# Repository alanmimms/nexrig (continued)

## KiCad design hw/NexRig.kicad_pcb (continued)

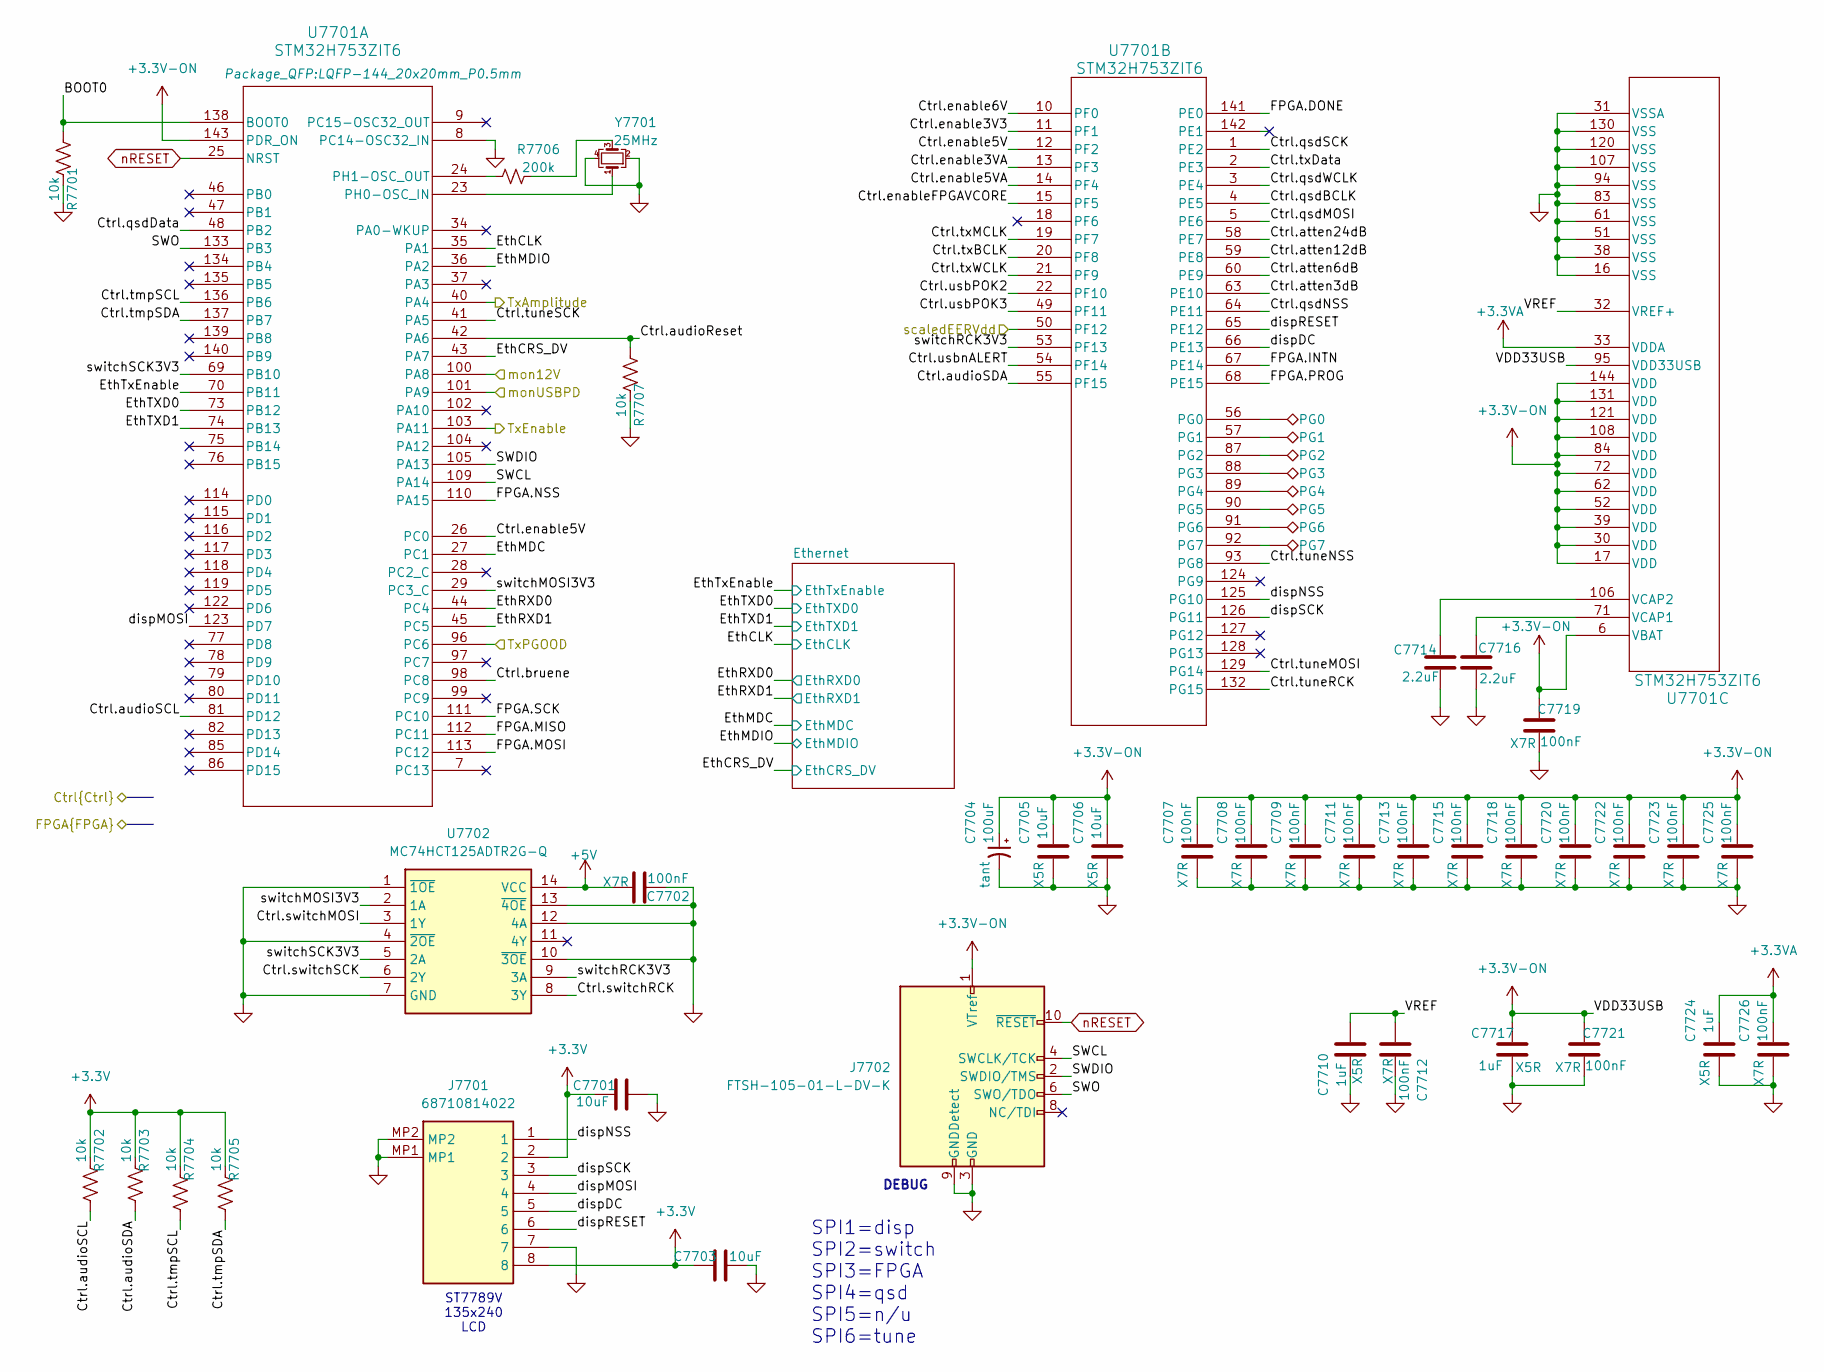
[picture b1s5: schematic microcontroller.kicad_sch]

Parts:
C7701, C7703, C7705, C7706: 10uF; C_0603_1608Metric; Manufacturer_Part_Number 81-GXT155R71E223KE1D; Mouser Part Number 963-MLAST168BB5106MT
C7702, C7707, C7708, C7709, C7711, C7712, C7713, C7715, C7718, C7719, C7720, C7721, C7722, C7723, C7725, C7726: 100nF; C_0603_1608Metric; Manufacturer_Part_Number C0805F104K1RACAUTO; Mouser Part Number 80-C0805F104K1RAUTO
C7704: 100uF; C_1206_3216Metric; Manufacturer_Part_Number TCTAL1A107M8R-V1; Mouser Part Number 755-TCTAL1A107M8R-V1
C7710, C7717, C7724: 1uF; C_0402_1005Metric; Manufacturer_Part_Number GRM155R61E105KE11D; Mouser Part Number 81-GRM155R61E105KE1D
C7714, C7716: 2.2uF; C_0805_2012Metric; Manufacturer_Part_Number TMCP1D225MTR2F; Mouser Part Number 74-TMCP1D225MTR2F
J7701: 68710814022; Mouser Part Number 710-68710814022
J7702: FTSH-105-01-L-DV-K; FTSH10501LDVK
PG7701: PG0; TestPoint_Pad_1.0x1.0mm
PG7702: PG1; TestPoint_Pad_1.0x1.0mm
PG7703: PG2; TestPoint_Pad_1.0x1.0mm
PG7704: PG3; TestPoint_Pad_1.0x1.0mm
PG7705: PG4; TestPoint_Pad_1.0x1.0mm
PG7706: PG5; TestPoint_Pad_1.0x1.0mm
PG7707: PG6; TestPoint_Pad_1.0x1.0mm
PG7708: PG7; TestPoint_Pad_1.0x1.0mm
R7701, R7702, R7703, R7704, R7705, R7707: 10k; R_0402_1005Metric
R7706: 200k; R_0603_1608Metric
U7701: STM32H753ZIT6; LQFP-144_20x20mm_P0.5mm
U7702: MC74HCT125ADTR2G-Q; SOP65P640X110-14N; Mouser Part Number 771-74HCT125PW-T
Y7701: 25MHz; Crystal_SMD_2520-4Pin_2.5x2.0mm; Manufacturer_Part_Number E2X250081G10; Mouser Part Number 504-E2X250081G10

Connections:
+3.3V: C7701.1, C7703.1, J7701.2, J7701.8, R7702.1, R7703.1, R7704.1, R7705.1; also elsewhere on the board
+3.3V-ON: C7704.1, C7705.1, C7706.1, C7707.1, C7708.1, C7709.1, C7711.1, C7713.1, C7715.1, C7717.1, C7718.1, C7719.1, C7720.1, C7721.1, C7722.1, C7723.1, C7725.1, J7702.1 (VTref), U7701.6 (VBAT), U7701.17 (VDD), U7701.30 (VDD), U7701.39 (VDD), U7701.52 (VDD), U7701.62 (VDD), U7701.72 (VDD), U7701.84 (VDD), U7701.95 (VDD33USB), U7701.108 (VDD), U7701.121 (VDD), U7701.131 (VDD), U7701.143 (PDR_ON), U7701.144 (VDD); also elsewhere on the board
+3.3VA: C7724.1, C7726.1, U7701.33 (VDDA); also elsewhere on the board
/FPGA/Ctrl.audioReset: R7707.1, U7701.42 (PA6); also elsewhere on the board
/FPGA/Ctrl.audioSCL: R7702.2, U7701.81 (PD12); also elsewhere on the board
/FPGA/Ctrl.audioSDA: R7703.2, U7701.55 (PF15); also elsewhere on the board
/FPGA/Ctrl.bruene: U7701.98 (PC8)
/FPGA/Ctrl.enable3V3: U7701.11 (PF1); also elsewhere on the board
/FPGA/Ctrl.enable3VA: U7701.13 (PF3); also elsewhere on the board
/FPGA/Ctrl.enable5V: U7701.12 (PF2), U7701.26 (PC0); also elsewhere on the board
/FPGA/Ctrl.enable5VA: U7701.14 (PF4); also elsewhere on the board
/FPGA/Ctrl.enable6V: U7701.10 (PF0); also elsewhere on the board
/FPGA/Ctrl.enableFPGAVCORE: U7701.15 (PF5)
/FPGA/Ctrl.qsdBCLK: U7701.4 (PE5); also elsewhere on the board
/FPGA/Ctrl.qsdData: U7701.48 (PB2); also elsewhere on the board
/FPGA/Ctrl.qsdMOSI: U7701.5 (PE6); also elsewhere on the board
/FPGA/Ctrl.qsdNSS: U7701.64 (PE11); also elsewhere on the board
/FPGA/Ctrl.qsdSCK: U7701.1 (PE2); also elsewhere on the board
/FPGA/Ctrl.qsdWCLK: U7701.3 (PE4); also elsewhere on the board
/FPGA/Ctrl.switchMOSI: U7702.3 (1Y); also elsewhere on the board
/FPGA/Ctrl.switchRCK: U7702.8 (3Y); also elsewhere on the board
/FPGA/Ctrl.switchSCK: U7702.6 (2Y); also elsewhere on the board
/FPGA/Ctrl.tmpSCL: R7704.2, U7701.136 (PB6); also elsewhere on the board
/FPGA/Ctrl.tmpSDA: R7705.2, U7701.137 (PB7); also elsewhere on the board
/FPGA/Ctrl.txBCLK: U7701.20 (PF8); also elsewhere on the board
/FPGA/Ctrl.txData: U7701.2 (PE3); also elsewhere on the board
/FPGA/Ctrl.txMCLK: U7701.19 (PF7); also elsewhere on the board
/FPGA/Ctrl.txWCLK: U7701.21 (PF9); also elsewhere on the board
/FPGA/Ctrl.usbPOK2: U7701.22 (PF10); also elsewhere on the board
/FPGA/Ctrl.usbPOK3: U7701.49 (PF11); also elsewhere on the board
/FPGA/Ctrl.usbnALERT: U7701.54 (PF14); also elsewhere on the board
/FPGA/FPGA.DONE: U7701.141 (PE0); also elsewhere on the board
/FPGA/FPGA.INTN: U7701.67 (PE14); also elsewhere on the board
/FPGA/FPGA.MISO: U7701.112 (PC11); also elsewhere on the board
/FPGA/FPGA.MOSI: U7701.113 (PC12); also elsewhere on the board
/FPGA/FPGA.NSS: U7701.110 (PA15); also elsewhere on the board
/FPGA/FPGA.PROG: U7701.68 (PE15); also elsewhere on the board
/FPGA/FPGA.SCK: U7701.111 (PC10); also elsewhere on the board
/Power/TxAmplitude: U7701.40 (PA4); also elsewhere on the board
/Power/TxEnable: U7701.103 (PA11); also elsewhere on the board
/Power/TxPGOOD: U7701.96 (PC6); also elsewhere on the board
/Power/mon12V: U7701.100 (PA8); also elsewhere on the board
/Power/monUSBPD: U7701.101 (PA9); also elsewhere on the board
/Power/scaledEERVdd: U7701.50 (PF12); also elsewhere on the board
/microcontroller/BOOT0: R7701.1, U7701.138 (BOOT0)
/microcontroller/Ctrl.atten3dB: U7701.63 (PE10)
/microcontroller/Ctrl.atten6dB: U7701.60 (PE9)
/microcontroller/Ctrl.atten12dB: U7701.59 (PE8)
/microcontroller/Ctrl.atten24dB: U7701.58 (PE7)
/microcontroller/Ctrl.tuneMOSI: U7701.129 (PG14)
/microcontroller/Ctrl.tuneNSS: U7701.93 (PG8)
/microcontroller/Ctrl.tuneRCK: U7701.132 (PG15)
/microcontroller/Ctrl.tuneSCK: U7701.41 (PA5)
/microcontroller/EthCLK: U7701.35 (PA1); also elsewhere on the board
/microcontroller/EthCRS_DV: U7701.43 (PA7); also elsewhere on the board
/microcontroller/EthMDC: U7701.27 (PC1); also elsewhere on the board
/microcontroller/EthMDIO: U7701.36 (PA2); also elsewhere on the board
/microcontroller/EthRXD0: U7701.44 (PC4); also elsewhere on the board
/microcontroller/EthRXD1: U7701.45 (PC5); also elsewhere on the board
/microcontroller/EthTXD0: U7701.73 (PB12); also elsewhere on the board
/microcontroller/EthTXD1: U7701.74 (PB13); also elsewhere on the board
/microcontroller/EthTxEnable: U7701.70 (PB11); also elsewhere on the board
/microcontroller/SWCL: J7702.4 (SWCLK/TCK), U7701.109 (PA14)
/microcontroller/SWDIO: J7702.2 (SWDIO/TMS), U7701.105 (PA13)
/microcontroller/SWO: J7702.6 (SWO/TDO), U7701.133 (PB3)
/microcontroller/VREF: C7710.1, C7712.1, U7701.32 (VREF+)
/microcontroller/dispDC: J7701.5, U7701.66 (PE13)
/microcontroller/dispMOSI: J7701.4, U7701.123 (PD7)
/microcontroller/dispNSS: J7701.1, U7701.125 (PG10)
/microcontroller/dispRESET: J7701.6, U7701.65 (PE12)
/microcontroller/dispSCK: J7701.3, U7701.126 (PG11)
/microcontroller/switchMOSI3V3: U7701.29 (PC3_C), U7702.2 (1A)
/microcontroller/switchRCK3V3: U7701.53 (PF13), U7702.9 (3A)
/microcontroller/switchSCK3V3: U7701.69 (PB10), U7702.5 (2A)
unnamed: R7706.2, Y7701.3
unnamed: U7701.23 (PH0-OSC_IN), Y7701.1
unnamed: R7706.1, U7701.24 (PH1-OSC_OUT)
unnamed: PG7701.1, U7701.56 (PG0)
unnamed: PG7702.1, U7701.57 (PG1)
unnamed: PG7703.1, U7701.87 (PG2)
unnamed: PG7704.1, U7701.88 (PG3)
unnamed: PG7705.1, U7701.89 (PG4)
unnamed: PG7706.1, U7701.90 (PG5)
unnamed: PG7707.1, U7701.91 (PG6)
unnamed: PG7708.1, U7701.92 (PG7)
unnamed: C7716.1, U7701.71 (VCAP1)
unnamed: C7714.1, U7701.106 (VCAP2)
nRESET: J7702.10 (~RESET), U7701.25 (NRST); also elsewhere on the board

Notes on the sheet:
SPI1=disp SPI2=switch SPI3=FPGA SPI4=qsd SPI5=n/u SPI6=tune
DEBUG
ST7789V 135x240 LCD

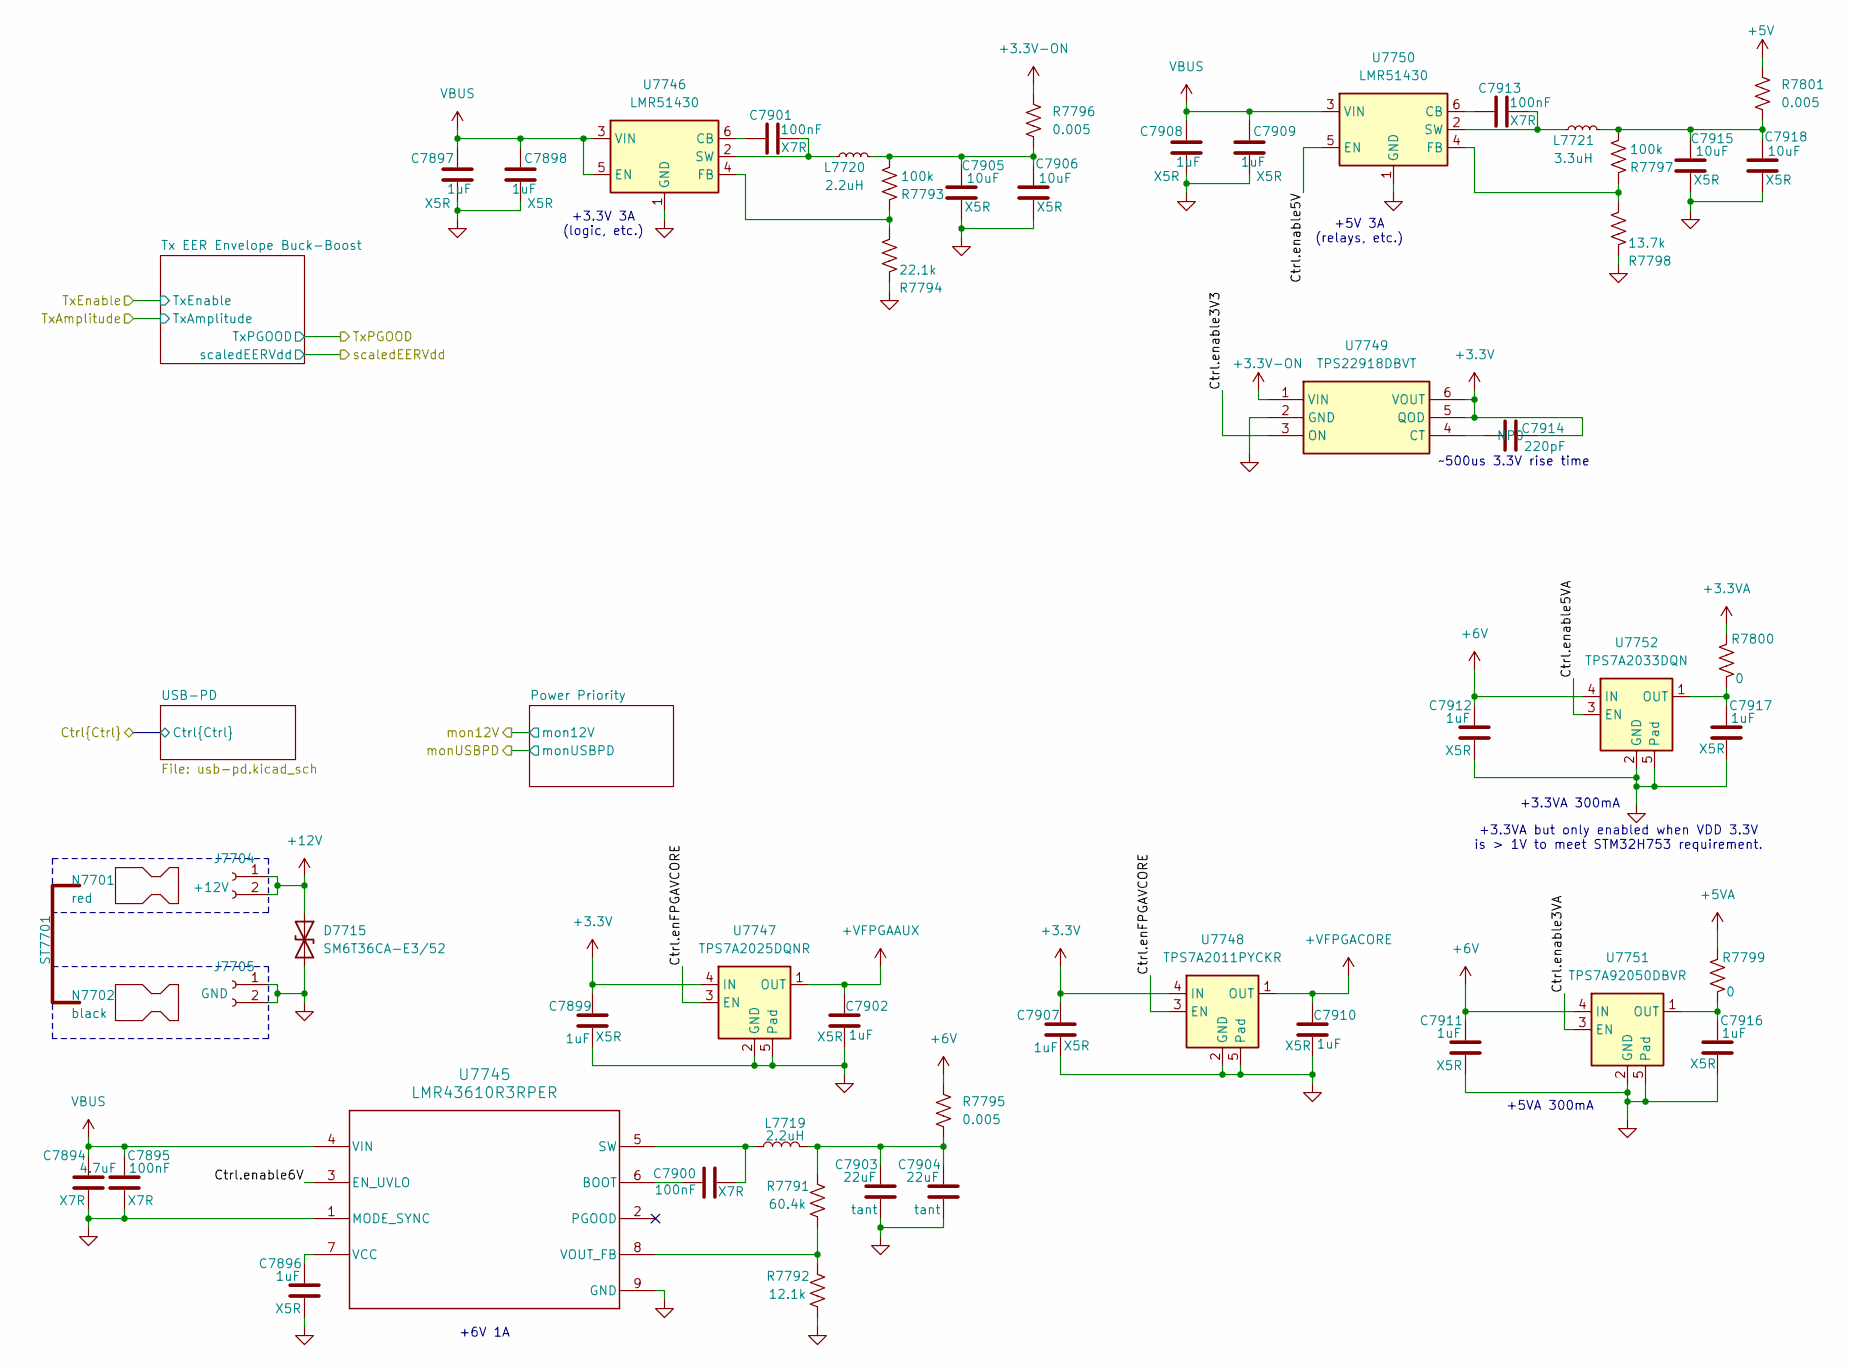
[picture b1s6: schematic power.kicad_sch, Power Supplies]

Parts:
C7894: 4.7uF; C_0805_2012Metric; Manufacturer_Part_Number 08055D475KAT4A; Mouser Part Number 581-08055D475KAT4A
C7895, C7900, C7901, C7913: 100nF; C_0603_1608Metric; Manufacturer_Part_Number C0805F104K1RACAUTO; Mouser Part Number 80-C0805F104K1RAUTO
C7896, C7899, C7902, C7907, C7910, C7911, C7912, C7916, C7917: 1uF; C_0402_1005Metric; Manufacturer_Part_Number GRM155R61E105KE11D; Mouser Part Number 81-GRM155R61E105KE1D
C7897, C7898, C7908, C7909: 1uF; C_0603_1608Metric; Manufacturer_Part_Number GRM155R61E105KE11D; Mouser Part Number 81-GRM155R61E105KE1D
C7903, C7904: 22uF; CP_EIA-7343-31_Kemet-D; Manufacturer_Part_Number 293D226X9035D2TE3; Mouser Part Number 74-293D226X9035D2TE3
C7905, C7906, C7915, C7918: 10uF; C_0603_1608Metric; Manufacturer_Part_Number 81-GXT155R71E223KE1D; Mouser Part Number 963-MLAST168BB5106MT
C7914: 220pF; C_0603_1608Metric; Manufacturer_Part_Number C1608C0G1H221F080AA; Mouser Part Number 810-C1608C0G1H221F
D7715: SM6T36CA-E3/52; D_SMB
J7704, J7705: 1336G1
L7719: 2.2uH; IND_XGL4030_COC
L7720: 2.2uH; L_0805_2012Metric
L7721: 3.3uH; L_0805_2012Metric
N7701: red
N7702: black
R7791: 60.4k; R_0603_1608Metric
R7792: 12.1k; R_0603_1608Metric
R7793, R7797: 100k; R_0402_1005Metric
R7794: 22.1k; R_0603_1608Metric
R7795, R7796, R7801: 0.005; R_0612_1632Metric; Manufacturer_Part_Number WFCP06125L000FE66
R7798: 13.7k; R_0603_1608Metric
R7799, R7800: 0; R_0603_1608Metric
ST7701: Anderson-114555P2-staple
U7745: LMR43610R3RPER; RPE0009A-MFG
U7746, U7750: LMR51430; SOT-23-6
U7747: TPS7A2025DQNR; Texas_X2SON-4_1x1mm_P0.65mm
U7748: TPS7A2011PYCKR; Texas_X2SON-4_1x1mm_P0.65mm
U7749: TPS22918DBVT; SOT-23-6; Mouser Part Number 595-TPS22918DBVT
U7751: TPS7A92050DBVR; Texas_X2SON-4_1x1mm_P0.65mm
U7752: TPS7A2033DQN; Texas_X2SON-4_1x1mm_P0.65mm

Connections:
+3.3V: C7899.1, C7907.1, C7914.2, U7747.4 (IN), U7748.4 (IN), U7749.5 (QOD), U7749.6 (VOUT); also elsewhere on the board
+3.3V-ON: R7796.1, U7749.1 (VIN); also elsewhere on the board
+3.3VA: R7800.1; also elsewhere on the board
+5VA: R7799.1; also elsewhere on the board
+6V: C7911.1, C7912.1, R7795.1, U7751.4 (IN), U7752.4 (IN)
+12V: D7715.1 (A1), J7704.1, J7704.2; also elsewhere on the board
+VFPGAAUX: C7902.1, U7747.1 (OUT); also elsewhere on the board
+VFPGACORE: C7910.1, U7748.1 (OUT); also elsewhere on the board
/FPGA/Ctrl.enable3V3: U7749.3 (ON); also elsewhere on the board
/FPGA/Ctrl.enable3VA: U7751.3 (EN); also elsewhere on the board
/FPGA/Ctrl.enable5V: U7750.5 (EN); also elsewhere on the board
/FPGA/Ctrl.enable5VA: U7752.3 (EN); also elsewhere on the board
/FPGA/Ctrl.enable6V: U7745.3 (EN_UVLO); also elsewhere on the board
/Power/Ctrl.enFPGAVCORE: U7747.3 (EN), U7748.3 (EN)
unnamed: C7903.1, C7904.1, L7719.2, R7791.2, R7795.2
unnamed: C7905.1, C7906.1, L7720.2, R7793.2, R7796.2
unnamed: C7915.1, C7918.1, L7721.2, R7797.2, R7801.2
unnamed: C7900.1, U7745.6 (BOOT)
unnamed: C7900.2, L7719.1, U7745.5 (SW)
unnamed: C7896.1, U7745.7 (VCC)
unnamed: R7791.1, R7792.2, U7745.8 (VOUT_FB)
unnamed: C7901.1, U7746.6 (CB)
unnamed: R7793.1, R7794.2, U7746.4 (FB)
unnamed: C7901.2, L7720.1, U7746.2 (SW)
unnamed: C7914.1, U7749.4 (CT)
unnamed: C7913.1, U7750.6 (CB)
unnamed: R7797.1, R7798.2, U7750.4 (FB)
unnamed: C7913.2, L7721.1, U7750.2 (SW)
unnamed: C7916.1, R7799.2, U7751.1 (OUT)
unnamed: C7917.1, R7800.2, U7752.1 (OUT)
VBUS: C7894.1, C7895.1, C7897.1, C7898.1, C7908.1, C7909.1, U7745.4 (VIN), U7746.3 (VIN), U7746.5 (EN), U7750.3 (VIN); also elsewhere on the board

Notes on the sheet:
~500us 3.3V rise time
+5V 3A (relays, etc.)
+6V 1A
+5VA 300mA
+3.3VA but only enabled when VDD 3.3V is > 1V to meet STM32H753 requirement.
+3.3V 3A (logic, etc.)
+3.3VA 300mA

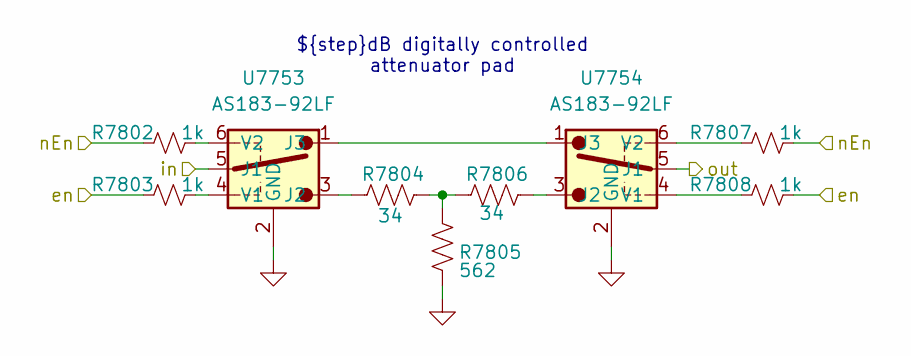
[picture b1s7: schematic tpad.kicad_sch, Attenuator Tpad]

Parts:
R7802, R7803, R7807, R7808: 1k; R_0402_1005Metric
R7804, R7806: 34; R_1206_3216Metric
R7805: 562; R_1206_3216Metric
U7753, U7754: AS183-92LF; SOT65P220X110-6N; Mouser Part Number 873-AS183-92LF

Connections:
/Rx Front End/Ctrl.atten3dB: R7803.1, R7808.2; also elsewhere on the board
/Rx Front End/Tpad 3/in: U7753.5 (J1); also elsewhere on the board
/Rx Front End/n3dB: R7802.1, R7807.2; also elsewhere on the board
/Rx Front End/rf200atten: U7754.5 (J1); also elsewhere on the board
unnamed: R7804.1, R7805.1, R7806.1
unnamed: R7804.2, U7753.3 (J2)
unnamed: U7753.1 (J3), U7754.1 (J3)
unnamed: R7803.2, U7753.4 (V1)
unnamed: R7802.2, U7753.6 (V2)
unnamed: R7806.2, U7754.3 (J2)
unnamed: R7808.1, U7754.4 (V1)
unnamed: R7807.1, U7754.6 (V2)

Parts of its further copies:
R7840, R7841, R7845, R7846, R7878, R7879, R7883, R7884, R7885, R7886, R7890, R7891: 1k; R_0402_1005Metric
R7842, R7844, R7880, R7882, R7887, R7889: 34; R_1206_3216Metric
R7843, R7881, R7888: 562; R_1206_3216Metric
U7761, U7762, U7767, U7768, U7769, U7770: AS183-92LF; SOT65P220X110-6N; Mouser Part Number 873-AS183-92LF

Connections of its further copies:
/Rx Front End/Ctrl.atten6dB: R7841.1, R7846.2; also elsewhere on the board
/Rx Front End/Ctrl.atten12dB: R7879.1, R7884.2; also elsewhere on the board
/Rx Front End/Ctrl.atten24dB: R7886.1, R7891.2; also elsewhere on the board
/Rx Front End/Tpad 3/in: U7762.5 (J1); also elsewhere on the board
/Rx Front End/Tpad 12/in: U7767.5 (J1), U7770.5 (J1)
/Rx Front End/Tpad 12/out: U7761.5 (J1), U7768.5 (J1)
/Rx Front End/Tpad 24/in: U7769.5 (J1); also elsewhere on the board
/Rx Front End/n6dB: R7840.1, R7845.2; also elsewhere on the board
/Rx Front End/n12dB: R7878.1, R7883.2; also elsewhere on the board
/Rx Front End/n24dB: R7885.1, R7890.2; also elsewhere on the board
unnamed: R7842.1, R7843.1, R7844.1
unnamed: R7880.1, R7881.1, R7882.1
unnamed: R7887.1, R7888.1, R7889.1
unnamed: R7842.2, U7761.3 (J2)
unnamed: U7761.1 (J3), U7762.1 (J3)
unnamed: R7841.2, U7761.4 (V1)
unnamed: R7840.2, U7761.6 (V2)
unnamed: R7844.2, U7762.3 (J2)
unnamed: R7846.1, U7762.4 (V1)
unnamed: R7845.1, U7762.6 (V2)
unnamed: R7880.2, U7767.3 (J2)
unnamed: U7767.1 (J3), U7768.1 (J3)
unnamed: R7879.2, U7767.4 (V1)
unnamed: R7878.2, U7767.6 (V2)
unnamed: R7882.2, U7768.3 (J2)
unnamed: R7884.1, U7768.4 (V1)
unnamed: R7883.1, U7768.6 (V2)
unnamed: R7887.2, U7769.3 (J2)
unnamed: U7769.1 (J3), U7770.1 (J3)
unnamed: R7886.2, U7769.4 (V1)
unnamed: R7885.2, U7769.6 (V2)
unnamed: R7889.2, U7770.3 (J2)
unnamed: R7891.1, U7770.4 (V1)
unnamed: R7890.1, U7770.6 (V2)

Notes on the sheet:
${step}dB digitally controlled attenuator pad

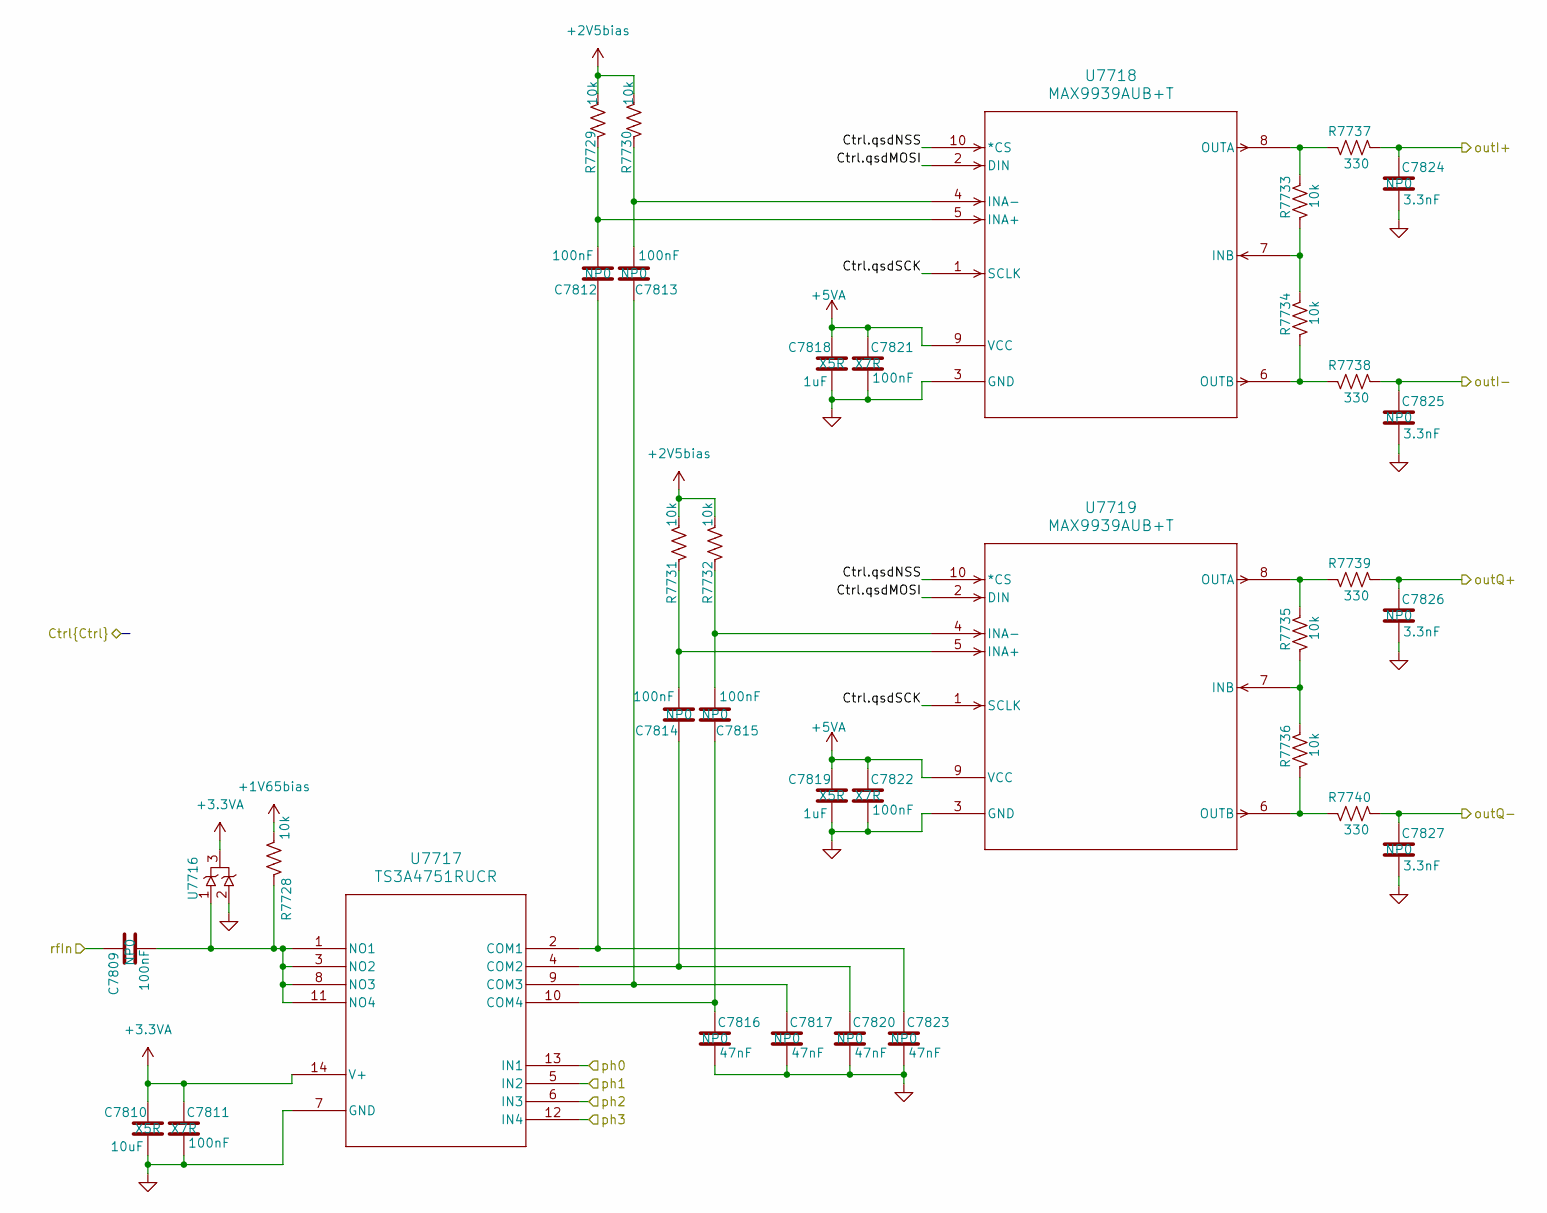
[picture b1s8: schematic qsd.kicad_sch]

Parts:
C7809, C7812, C7813, C7814, C7815: 100nF; C_1206_3216Metric; Manufacturer_Part_Number GRM31C5C2A104JA01L; Mouser Part Number 81-GRM31C5C2A104JA1L
C7810: 10uF; C_0603_1608Metric; Manufacturer_Part_Number 81-GXT155R71E223KE1D; Mouser Part Number 963-MLAST168BB5106MT
C7811, C7821, C7822: 100nF; C_0603_1608Metric; Manufacturer_Part_Number C0805F104K1RACAUTO; Mouser Part Number 80-C0805F104K1RAUTO
C7816, C7817, C7820, C7823: 47nF; C_0805_2012Metric; Manufacturer_Part_Number GCM31M5C1H473FA16L; Mouser Part Number 81-GCM31M5C1H473FA6L
C7818, C7819: 1uF; C_0402_1005Metric; Manufacturer_Part_Number GRM155R61E105KE11D; Mouser Part Number 81-GRM155R61E105KE1D
C7824, C7825, C7826, C7827: 3.3nF; C_0603_1608Metric; Manufacturer_Part_Number C1608C0G1H332J080AE; Mouser Part Number 810-C1608C0G1H332J08
R7728, R7729, R7730, R7731, R7732, R7733, R7734, R7735, R7736: 10k; R_0402_1005Metric
R7737, R7738, R7739, R7740: 330; R_0603_1608Metric
U7716: SZNUP1105LT1G; SOT-23
U7717: TS3A4751RUCR; TS3A4751-RUC14
U7718, U7719: MAX9939AUB+T; 21-0061L_MXM

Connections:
+1V65bias: R7728.1; also elsewhere on the board
+2V5bias: R7729.1, R7730.1, R7731.1, R7732.1; also elsewhere on the board
+3.3VA: C7810.1, C7811.1, U7716.3, U7717.14 (V+); also elsewhere on the board
+5VA: C7818.1, C7819.1, C7821.1, C7822.1, U7718.9 (VCC), U7719.9 (VCC); also elsewhere on the board
/FPGA/Ctrl.qsdMOSI: U7718.2 (DIN), U7719.2 (DIN); also elsewhere on the board
/FPGA/Ctrl.qsdNSS: U7718.10 (*CS), U7719.10 (*CS); also elsewhere on the board
/FPGA/Ctrl.qsdPh1a: U7717.13 (IN1); also elsewhere on the board
/FPGA/Ctrl.qsdPh1b: U7717.5 (IN2); also elsewhere on the board
/FPGA/Ctrl.qsdPh1c: U7717.6 (IN3); also elsewhere on the board
/FPGA/Ctrl.qsdPh1d: U7717.12 (IN4); also elsewhere on the board
/FPGA/Ctrl.qsdSCK: U7718.1 (SCLK), U7719.1 (SCLK); also elsewhere on the board
/Rx Front End/QSD1/rfIn: C7809.1; also elsewhere on the board
/Rx Front End/RxI1n: C7825.1, R7738.2; also elsewhere on the board
/Rx Front End/RxI1p: C7824.1, R7737.2; also elsewhere on the board
/Rx Front End/RxQ1n: C7827.1, R7740.2; also elsewhere on the board
/Rx Front End/RxQ1p: C7826.1, R7739.2; also elsewhere on the board
unnamed: C7812.1, C7823.1, U7717.2 (COM1)
unnamed: C7814.1, C7820.1, U7717.4 (COM2)
unnamed: C7813.1, C7817.1, U7717.9 (COM3)
unnamed: C7815.1, C7816.1, U7717.10 (COM4)
unnamed: C7809.2, R7728.2, U7716.1, U7717.1 (NO1), U7717.3 (NO2), U7717.8 (NO3), U7717.11 (NO4)
unnamed: C7812.2, R7729.2, U7718.5 (INA+)
unnamed: C7813.2, R7730.2, U7718.4 (INA-)
unnamed: R7733.2, R7734.1, U7718.7 (INB)
unnamed: R7733.1, R7737.1, U7718.8 (OUTA)
unnamed: R7734.2, R7738.1, U7718.6 (OUTB)
unnamed: C7814.2, R7731.2, U7719.5 (INA+)
unnamed: C7815.2, R7732.2, U7719.4 (INA-)
unnamed: R7735.2, R7736.1, U7719.7 (INB)
unnamed: R7735.1, R7739.1, U7719.8 (OUTA)
unnamed: R7736.2, R7740.1, U7719.6 (OUTB)

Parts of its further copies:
C7828, C7831, C7832, C7833, C7834, C7847, C7850, C7851, C7852, C7853: 100nF; C_1206_3216Metric; Manufacturer_Part_Number GRM31C5C2A104JA01L; Mouser Part Number 81-GRM31C5C2A104JA1L
C7829, C7848: 10uF; C_0603_1608Metric; Manufacturer_Part_Number 81-GXT155R71E223KE1D; Mouser Part Number 963-MLAST168BB5106MT
C7830, C7840, C7841, C7849, C7859, C7860: 100nF; C_0603_1608Metric; Manufacturer_Part_Number C0805F104K1RACAUTO; Mouser Part Number 80-C0805F104K1RAUTO
C7835, C7836, C7839, C7842, C7854, C7855, C7858, C7861: 47nF; C_0805_2012Metric; Manufacturer_Part_Number GCM31M5C1H473FA16L; Mouser Part Number 81-GCM31M5C1H473FA6L
C7837, C7838, C7856, C7857: 1uF; C_0402_1005Metric; Manufacturer_Part_Number GRM155R61E105KE11D; Mouser Part Number 81-GRM155R61E105KE1D
C7843, C7844, C7845, C7846, C7862, C7863, C7864, C7865: 3.3nF; C_0603_1608Metric; Manufacturer_Part_Number C1608C0G1H332J080AE; Mouser Part Number 810-C1608C0G1H332J08
R7741, R7742, R7743, R7744, R7745, R7746, R7747, R7748, R7749, R7754, R7755, R7756, R7757, R7758, R7759, R7760, R7761, R7762: 10k; R_0402_1005Metric
R7750, R7751, R7752, R7753, R7763, R7764, R7765, R7766: 330; R_0603_1608Metric
U7720, U7724: SZNUP1105LT1G; SOT-23
U7721, U7725: TS3A4751RUCR; TS3A4751-RUC14
U7722, U7723, U7726, U7727: MAX9939AUB+T; 21-0061L_MXM

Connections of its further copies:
+1V65bias: R7741.1, R7754.1; also elsewhere on the board
+2V5bias: R7742.1, R7743.1, R7744.1, R7745.1, R7755.1, R7756.1, R7757.1, R7758.1; also elsewhere on the board
+3.3VA: C7829.1, C7830.1, C7848.1, C7849.1, U7720.3, U7721.14 (V+), U7724.3, U7725.14 (V+); also elsewhere on the board
+5VA: C7837.1, C7838.1, C7840.1, C7841.1, C7856.1, C7857.1, C7859.1, C7860.1, U7722.9 (VCC), U7723.9 (VCC), U7726.9 (VCC), U7727.9 (VCC); also elsewhere on the board
/FPGA/Ctrl.qsdMOSI: U7722.2 (DIN), U7723.2 (DIN), U7726.2 (DIN), U7727.2 (DIN); also elsewhere on the board
/FPGA/Ctrl.qsdNSS: U7722.10 (*CS), U7723.10 (*CS), U7726.10 (*CS), U7727.10 (*CS); also elsewhere on the board
/FPGA/Ctrl.qsdPh0a: U7725.13 (IN1); also elsewhere on the board
/FPGA/Ctrl.qsdPh0b: U7725.5 (IN2); also elsewhere on the board
/FPGA/Ctrl.qsdPh0c: U7725.6 (IN3); also elsewhere on the board
/FPGA/Ctrl.qsdPh0d: U7725.12 (IN4); also elsewhere on the board
/FPGA/Ctrl.qsdPh2a: U7721.13 (IN1); also elsewhere on the board
/FPGA/Ctrl.qsdPh2b: U7721.5 (IN2); also elsewhere on the board
/FPGA/Ctrl.qsdPh2c: U7721.6 (IN3); also elsewhere on the board
/FPGA/Ctrl.qsdPh2d: U7721.12 (IN4); also elsewhere on the board
/FPGA/Ctrl.qsdSCK: U7722.1 (SCLK), U7723.1 (SCLK), U7726.1 (SCLK), U7727.1 (SCLK); also elsewhere on the board
/Rx Front End/QSD0/rfIn: C7847.1; also elsewhere on the board
/Rx Front End/QSD2/rfIn: C7828.1; also elsewhere on the board
/Rx Front End/RxI0n: C7863.1, R7764.2
/Rx Front End/RxI0p: C7862.1, R7763.2; also elsewhere on the board
/Rx Front End/RxI2n: C7844.1, R7751.2; also elsewhere on the board
/Rx Front End/RxI2p: C7843.1, R7750.2; also elsewhere on the board
/Rx Front End/RxQ0n: C7865.1, R7766.2
/Rx Front End/RxQ0p: C7864.1, R7765.2; also elsewhere on the board
/Rx Front End/RxQ2n: C7846.1, R7753.2; also elsewhere on the board
/Rx Front End/RxQ2p: C7845.1, R7752.2; also elsewhere on the board
unnamed: C7831.1, C7842.1, U7721.2 (COM1)
unnamed: C7833.1, C7839.1, U7721.4 (COM2)
unnamed: C7832.1, C7836.1, U7721.9 (COM3)
unnamed: C7834.1, C7835.1, U7721.10 (COM4)
unnamed: C7828.2, R7741.2, U7720.1, U7721.1 (NO1), U7721.3 (NO2), U7721.8 (NO3), U7721.11 (NO4)
unnamed: C7831.2, R7742.2, U7722.5 (INA+)
unnamed: C7832.2, R7743.2, U7722.4 (INA-)
unnamed: R7746.2, R7747.1, U7722.7 (INB)
unnamed: R7746.1, R7750.1, U7722.8 (OUTA)
unnamed: R7747.2, R7751.1, U7722.6 (OUTB)
unnamed: C7833.2, R7744.2, U7723.5 (INA+)
unnamed: C7834.2, R7745.2, U7723.4 (INA-)
unnamed: R7748.2, R7749.1, U7723.7 (INB)
unnamed: R7748.1, R7752.1, U7723.8 (OUTA)
unnamed: R7749.2, R7753.1, U7723.6 (OUTB)
unnamed: C7850.1, C7861.1, U7725.2 (COM1)
unnamed: C7852.1, C7858.1, U7725.4 (COM2)
unnamed: C7851.1, C7855.1, U7725.9 (COM3)
unnamed: C7853.1, C7854.1, U7725.10 (COM4)
unnamed: C7847.2, R7754.2, U7724.1, U7725.1 (NO1), U7725.3 (NO2), U7725.8 (NO3), U7725.11 (NO4)
unnamed: C7850.2, R7755.2, U7726.5 (INA+)
unnamed: C7851.2, R7756.2, U7726.4 (INA-)
unnamed: R7759.2, R7760.1, U7726.7 (INB)
unnamed: R7759.1, R7763.1, U7726.8 (OUTA)
unnamed: R7760.2, R7764.1, U7726.6 (OUTB)
unnamed: C7852.2, R7757.2, U7727.5 (INA+)
unnamed: C7853.2, R7758.2, U7727.4 (INA-)
unnamed: R7761.2, R7762.1, U7727.7 (INB)
unnamed: R7761.1, R7765.1, U7727.8 (OUTA)
unnamed: R7762.2, R7766.1, U7727.6 (OUTB)
